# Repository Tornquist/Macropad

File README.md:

# Macropad

A 12-key 4x3 macropad for Cherry MX Switches designed in Eagle and
configured with QMK.

* [PCB](PCB/)
* [Bill of Materials](BOM.md)
* [Firmware](Firmware/)

## Assembled Board

## Keymap

| Base                          | Raised                        |
|:-----------------------------:|:-----------------------------:|
|    |  |

## PCB

| Top                        | Bottom                     |
|:--------------------------:|:--------------------------:|
|     |  |

## Schematic

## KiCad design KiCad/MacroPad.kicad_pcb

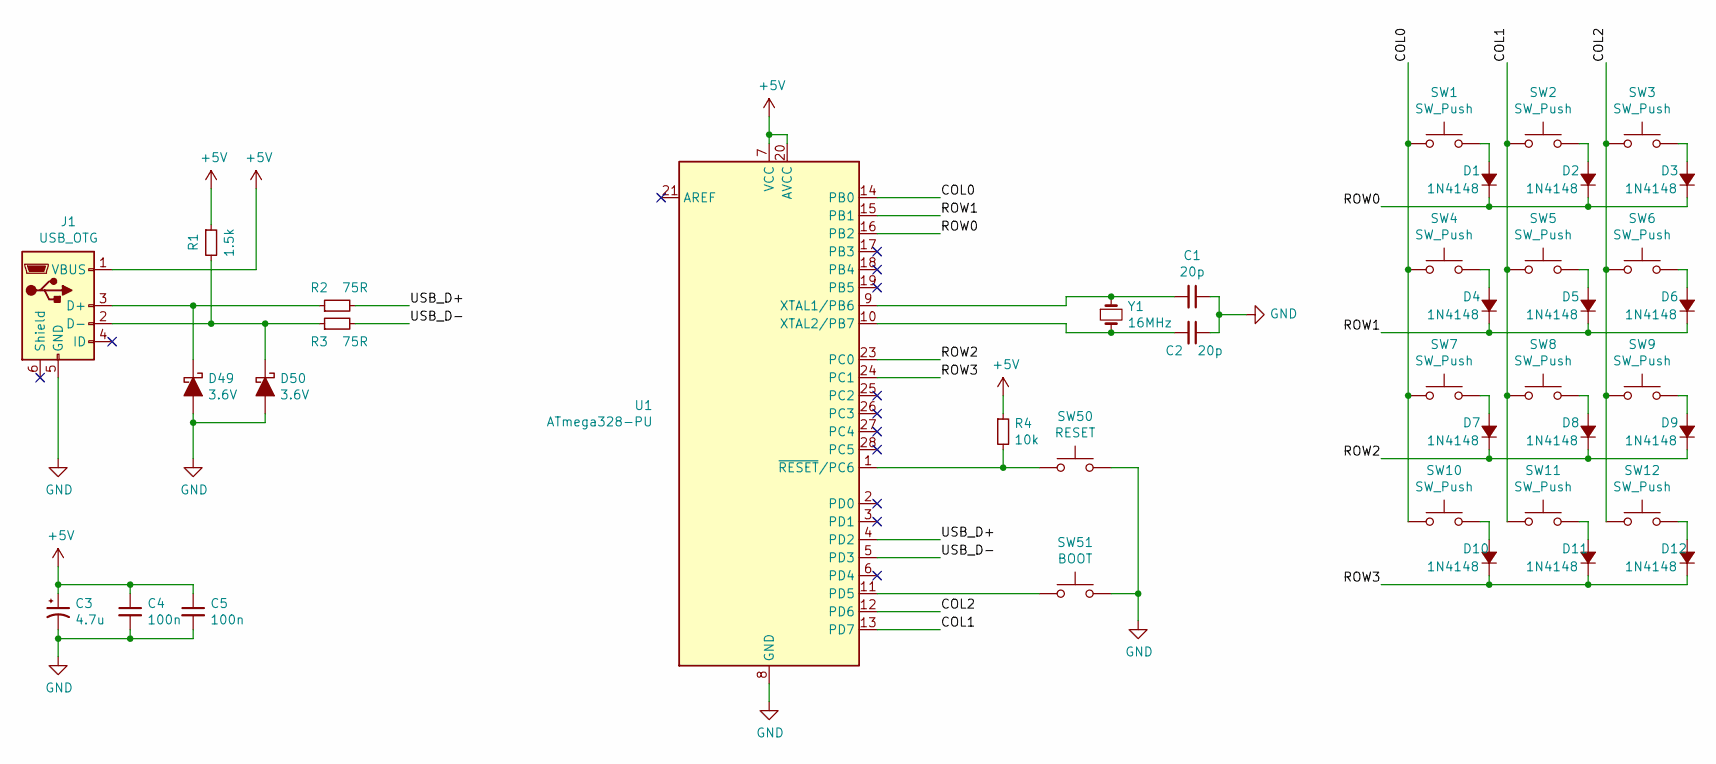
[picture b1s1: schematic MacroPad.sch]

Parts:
C1, C2: 20p; C_Disc_D3.0mm_W1.6mm_P2.50mm
C3: 4.7u; CP_Radial_D4.0mm_P1.50mm
C4, C5: 100n; C_Disc_D4.3mm_W1.9mm_P5.00mm
D1, D2, D3, D4, D5, D6, D7, D8, D9, D10, D11, D12: 1N4148; D_DO-35_SOD27_P5.08mm_Vertical_KathodeUp
D49, D50: 3.6V; D_DO-35_SOD27_P5.08mm_Vertical_KathodeUp
J1: USB_OTG; USB_Mini-B_Lumberg_2486_01_Horizontal
R1: 1.5k; R_Axial_DIN0204_L3.6mm_D1.6mm_P5.08mm_Horizontal
R2, R3: 75R; R_Axial_DIN0204_L3.6mm_D1.6mm_P5.08mm_Horizontal
R4: 10k; R_Axial_DIN0204_L3.6mm_D1.6mm_P5.08mm_Horizontal
SW1, SW2, SW3, SW4, SW5, SW6, SW7, SW8, SW9, SW10, SW11, SW12: SW_Push; SW_Cherry_MX1A_1.00u_PCB
SW50: RESET; SW_PUSH_6mm
SW51: BOOT; SW_PUSH_6mm
U1: ATmega328-PU; DIP-28_W7.62mm
Y1: 16MHz; Crystal_HC49-4H_Vertical

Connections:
+5V: C3.1, C4.1, C5.1, J1.1 (VBUS), R1.1, R4.1, U1.7 (VCC), U1.20 (AVCC)
/COL0: SW1.1, SW4.1, SW7.1, SW10.1, U1.14 (PB0)
/COL1: SW2.1, SW5.1, SW8.1, SW11.1, U1.13 (PD7)
/COL2: SW3.1, SW6.1, SW9.1, SW12.1, U1.12 (PD6)
/ROW0: D1.1 (K), D2.1 (K), D3.1 (K), U1.16 (PB2)
/ROW1: D4.1 (K), D5.1 (K), D6.1 (K), U1.15 (PB1)
/ROW2: D7.1 (K), D8.1 (K), D9.1 (K), U1.23 (PC0)
/ROW3: D10.1 (K), D11.1 (K), D12.1 (K), U1.24 (PC1)
/USB_D+: R2.2, U1.4 (PD2)
/USB_D-: R3.2, U1.5 (PD3)
GND: C1.1, C2.1, C3.2, C4.2, C5.2, D49.2 (A), D50.2 (A), J1.5 (GND), SW50.2, SW51.2, U1.8 (GND), U1.22 (GND)
unnamed: C1.2, U1.9 (XTAL1/PB6), Y1.1
unnamed: C2.2, U1.10 (XTAL2/PB7), Y1.2
unnamed: D1.2 (A), SW1.2
unnamed: D2.2 (A), SW2.2
unnamed: D3.2 (A), SW3.2
unnamed: D4.2 (A), SW4.2
unnamed: D5.2 (A), SW5.2
unnamed: D6.2 (A), SW6.2
unnamed: D7.2 (A), SW7.2
unnamed: D8.2 (A), SW8.2
unnamed: D9.2 (A), SW9.2
unnamed: D10.2 (A), SW10.2
unnamed: D11.2 (A), SW11.2
unnamed: D12.2 (A), SW12.2
unnamed: D49.1 (K), J1.3 (D+), R2.1
unnamed: D50.1 (K), J1.2 (D-), R1.2, R3.1
unnamed: R4.2, SW50.1, U1.1 (~RESET~/PC6)
unnamed: SW51.1, U1.11 (PD5)

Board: 2 copper layers, 40 parts (0 on the bottom side), 29 nets, no tracks yet.

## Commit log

2019-05-17 Connect processor to usb and power
2019-05-17 Add switch array and connect to microcontroller
2019-05-17 Rough board estimation: checking size
2019-05-18 Move Eagle into /Eagle and add KiCad/* schematic
2019-05-18 Keyboard schematic with associated parts
2019-05-18 Arrange components for size analysis with accurate mx switches
2019-05-21 Redo schematic in Eagle using clueboard library
2019-05-21 Create schematic and start aligning pin order
2019-05-21 Update switch and chip footprints, and switch array pins
2019-05-21 Route rows
2019-05-21 Route columns
2019-05-21 Routed board
2019-05-22 Compress row traces
2019-05-22 Components routed in compressed area
2019-05-22 Shrink board
2019-05-23 Redone schematic with smaller capacitors, fixed decoupling capacitors, and adjusted trace sizes
2019-05-23 Add top and bottom ground plane and merge gnd and ugnd
2019-05-23 Reduce acute angles and move vias farther from board
2019-05-23 Align all labels
2019-05-25 Update layout with appropriate spacing between switches (100mil border)
2019-05-25 Adjust vias position based on JLCPCB rendering
2019-05-25 Add version number to board
2019-05-25 Add Bill of Materials and README
2019-05-25 Remove working schematics and move v20190525 to PCB/
2019-06-08 Replace surface mount diodes with through hole
2019-06-08 Swap GFN for TQFP Chip -- board not updated
2019-06-08 Update board for TQFP footprint
2019-06-08 Use 5x3.2mm crystal
2019-06-08 Reroute columns to avoid vias
2019-06-08 Rename components based on board position
2019-06-08 Add label for chip orientation
2019-06-09 Add links to other components
2019-06-09 Finishing Touches: Date, cam file, row 2 routing, chip orientation indicator
2019-06-09 Use ATMEGA32U4-AU
2019-06-20 Add QMK Keyboard configuration
2019-06-20 Update PCB to correct D- and D+ mapping. Increment Date
2019-06-20 Add details on firmware flashing
2019-06-20 Added PCB Readme with eagle references
2019-06-20 Add schematic
2019-06-20 Add top and bottom pcb images
2019-06-20 Add assembled image and keymaps

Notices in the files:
parts and their libraries:
SparkFun-Clocks: Licensing: Creative Commons ShareAlike 4.0 International - https://creativecommons.org/licenses/by-sa/4.0
